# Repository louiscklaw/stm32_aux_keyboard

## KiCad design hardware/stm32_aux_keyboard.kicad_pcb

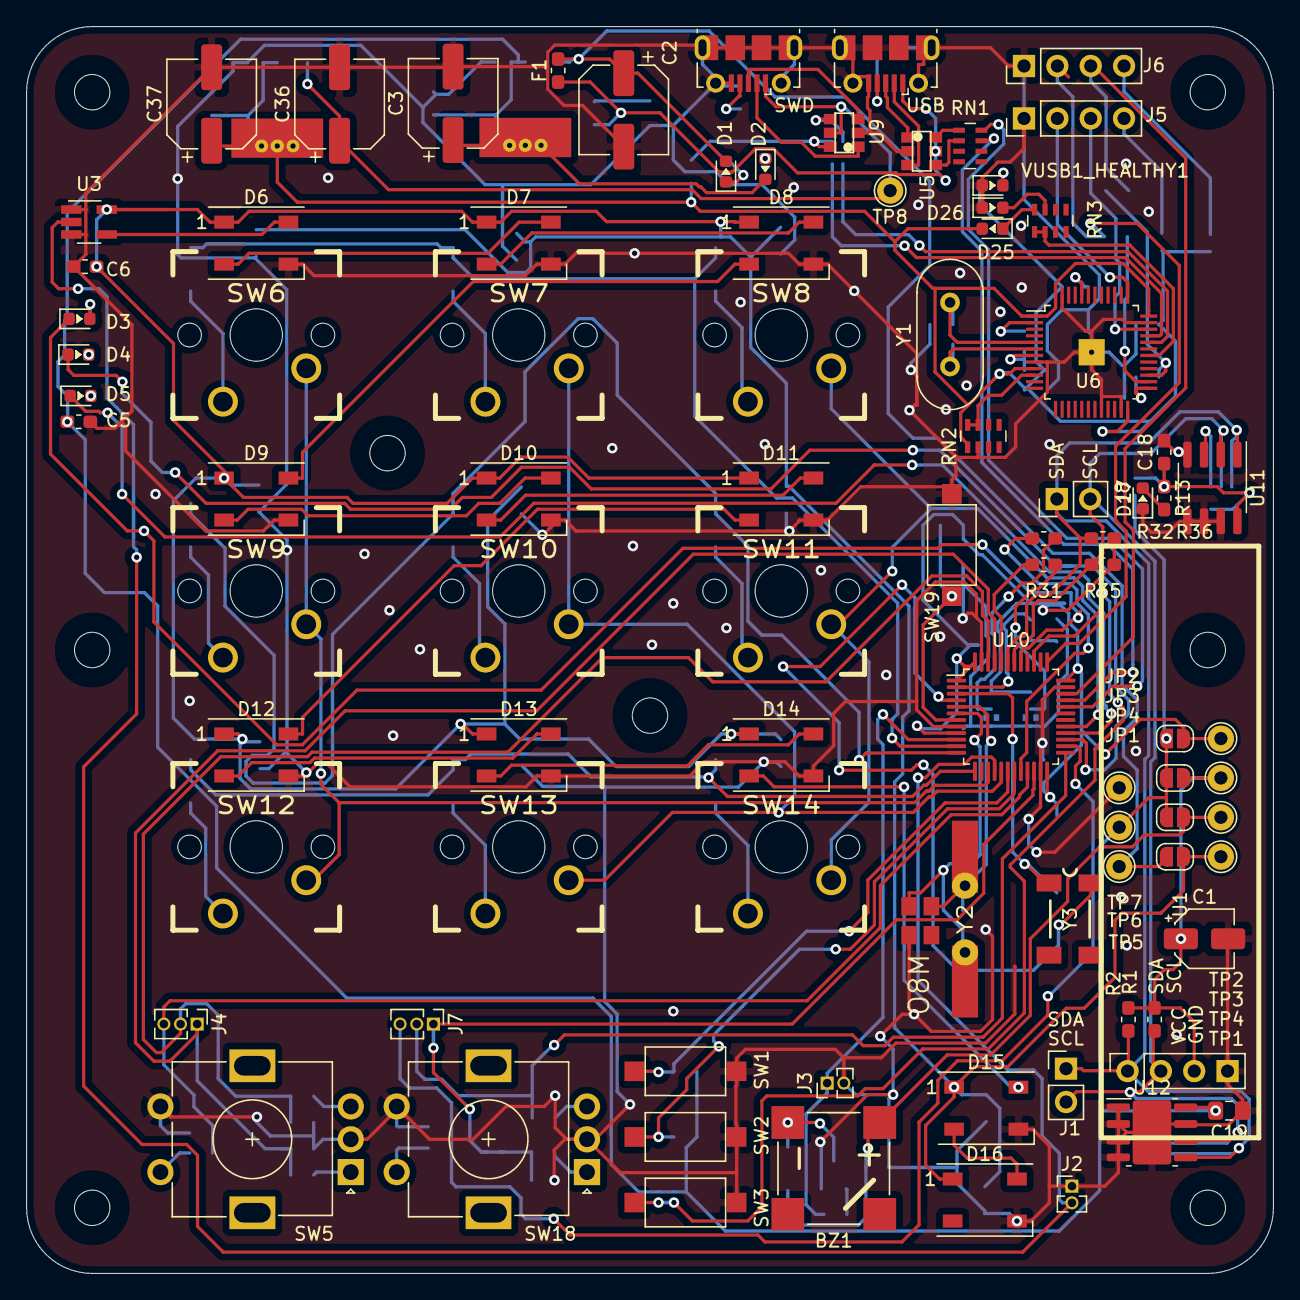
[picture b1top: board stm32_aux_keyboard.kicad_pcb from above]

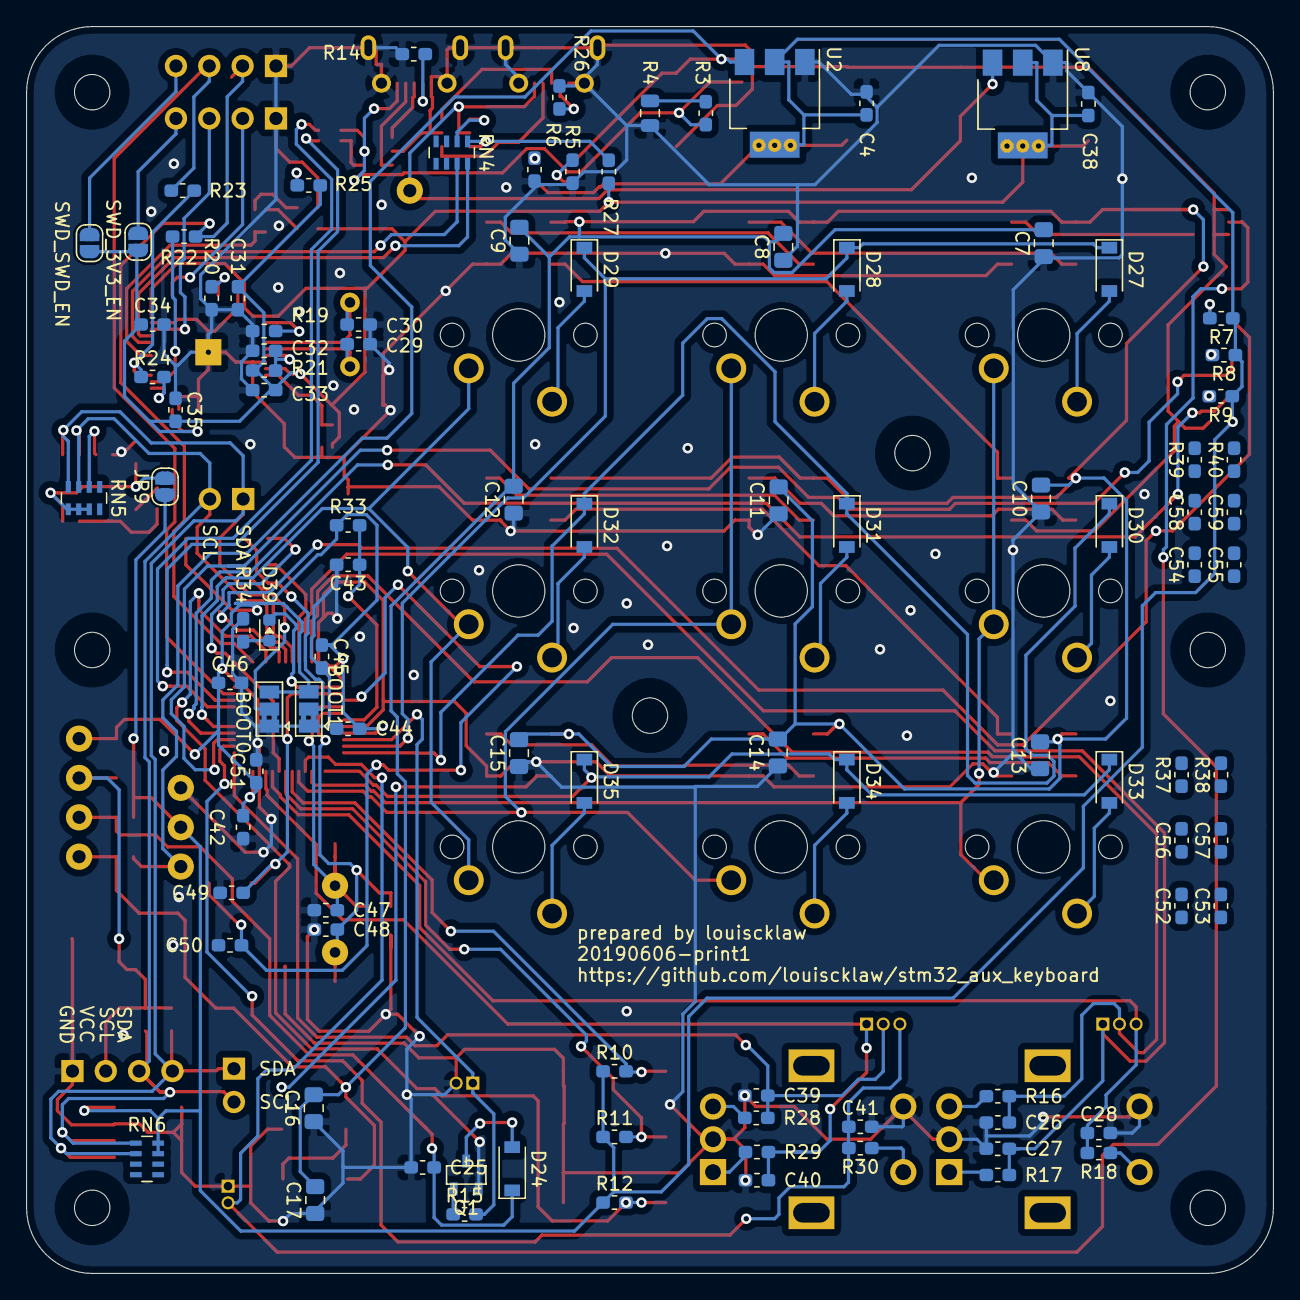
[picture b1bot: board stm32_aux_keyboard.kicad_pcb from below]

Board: 2 copper layers, 95.0 x 95.0 mm, 197 parts (100 on the bottom side), 113 nets.

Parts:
BZ1: BUZZER,MLT-8530; MLT-8530
C1: CP10uf,16V; CP_Elec_4x5.3
C2, C3, C36, C37: CP100uf,16V; CP_Elec_6.3x5.3
C4, C38: C105; C_0603_1608Metric_Pad1.05x0.95mm_HandSolder
C5, C6, C25: C106,0603; C_0603_1608Metric_Pad1.05x0.95mm_HandSolder
C7, C8, C9, C10, C11, C12, C13, C14, C15, C16, C17, C19: C106,0805; C_0805_2012Metric_Pad1.15x1.40mm_HandSolder
C18: C103,0603; C_0603_1608Metric_Pad1.05x0.95mm_HandSolder
C26, C27, C28, C31, C32, C33, C34, C35, C39, C40, C41, C42, C44, C45, C46, C51: C104,0603; C_0603_1608Metric_Pad1.05x0.95mm_HandSolder
C29, C30: C20pf,0603; C_0603_1608Metric_Pad1.05x0.95mm_HandSolder
C43: C105,0603; C_0603_1608Metric_Pad1.05x0.95mm_HandSolder
C47, C48, C49, C50: C20pf; C_0603_1608Metric_Pad1.05x0.95mm_HandSolder
C52, C53, C54, C55, C56, C57, C58, C59: SPARE,0603; C_0603_1608Metric_Pad1.05x0.95mm_HandSolder
D1: LED_GREEN; LED_0603_1608Metric
D2: LED_ORANGE; LED_0603_1608Metric
D3: USR_LED_1; LED_0603_1608Metric
D4: USR_LED_2; LED_0603_1608Metric
D5: USR_LED_3; LED_0603_1608Metric
D6, D7, D8, D9, D10, D11, D12, D13, D14, D15, D16: WS2812B; LED_WS2812B_5050_white
D17, D25: LED_GREEN,0603; LED_0603_1608Metric
D24, D27, D28, D29, D30, D31, D32, D33, D34, D35: D_1N4148_T4; D_SOD-123
D26: LED_RED,0603; LED_0603_1608Metric
D39: PC13; LED_0603_1608Metric
F1: Fuse_Small; R_0603_1608Metric_Pad1.05x0.95mm_HandSolder
H1, H2, H3, H4, H5, H6, H7, H8: MOUNT_M2; MountingHole_2.7mm_M2.5,rpi_like
J1, J8: I2C_HEADER,2.54; I2C_DEBUG,2.54
J2: WS2812_HEADER; PinHeader_1x02_P1.27mm_Vertical
J3: BUZZER_HEADER; PinHeader_1x02_P1.27mm_Vertical
J4, J7: ROT_ENC_HEADER; PinHeader_1x03_P1.27mm_Vertical
J5, J6: SWD_SWD; BLUEPILL_SWD
JP1: WS2812_EN; SolderJumper-2_P1.3mm_Open_RoundedPad1.0x1.5mm
JP2: STM32_EN; SolderJumper-2_P1.3mm_Open_RoundedPad1.0x1.5mm
JP3: OLED_EN; SolderJumper-2_P1.3mm_Open_RoundedPad1.0x1.5mm
JP4: BUZZER_EN; SolderJumper-2_P1.3mm_Open_RoundedPad1.0x1.5mm
JP5: SWD_3V3_EN; SolderJumper-2_P1.3mm_Open_RoundedPad1.0x1.5mm
JP6: SWD_SWD_EN; SolderJumper-2_P1.3mm_Open_RoundedPad1.0x1.5mm
JP7: BOOT0; SolderJumper-3_P1.3mm_Bridged2Bar12_Pad1.0x1.5mm
JP8: BOOT1; SolderJumper-3_P1.3mm_Bridged2Bar12_Pad1.0x1.5mm
JP9: EN; SolderJumper-2_P1.3mm_Open_RoundedPad1.0x1.5mm
Q1: SS9013_J3; 9013,J3,SOT23
R1, R2, R35, R36: R472,0603; R_0603_1608Metric_Pad1.05x0.95mm_HandSolder
R3, R37, R38, R39, R40: R0,0603; R_0603_1608Metric_Pad1.05x0.95mm_HandSolder
R4: VAR_5V6,0805; VAR_0805
R5, R6, R34: R511,0603; R_0603_1608Metric_Pad1.05x0.95mm_HandSolder
R7, R8, R9, R10, R11, R12, R13, R33: R103,0603; R_0603_1608Metric_Pad1.05x0.95mm_HandSolder
R14, R19, R20, R21, R26: R104,0603; R_0603_1608Metric_Pad1.05x0.95mm_HandSolder
R15: R471,0603; R_0603_1608Metric_Pad1.05x0.95mm_HandSolder
R16, R17, R18, R28, R29, R30: R273,0603; R_0603_1608Metric_Pad1.05x0.95mm_HandSolder
R22, R23: R220,0603; R_0603_1608Metric_Pad1.05x0.95mm_HandSolder
R24: R101,0603; R_0603_1608Metric_Pad1.05x0.95mm_HandSolder
R25: R221,0603; R_0603_1608Metric_Pad1.05x0.95mm_HandSolder
R27: R152,0603; R_0603_1608Metric_Pad1.05x0.95mm_HandSolder
R31, R32: R104; R_0603_1608Metric_Pad1.05x0.95mm_HandSolder
RN1: RN_220,0603; R_Array_Concave_4x0603
RN2, RN5, RN6: RN_472,0603; R_Array_Concave_4x0603
RN3, RN4: RN_221,0603; R_Array_Concave_4x0603
SW1: USR_BTN_1; SW_SPST_CK_RS282G05A3
SW2: USR_BTN_2; SW_SPST_CK_RS282G05A3
SW3: USR_BTN_3; SW_SPST_CK_RS282G05A3
SW5: ROT2; RotaryEncoder_Alps_EC11E_Vertical_H20mm
SW6: KEY11; cherry_mx_without_led_100H
SW7: KEY12; cherry_mx_without_led_100H
SW8: KEY13; cherry_mx_without_led_100H
SW9: KEY21; cherry_mx_without_led_100H
SW10: KEY22; cherry_mx_without_led_100H
SW11: KEY23; cherry_mx_without_led_100H
SW12: KEY31; cherry_mx_without_led_100H
SW13: KEY32; cherry_mx_without_led_100H
SW14: KEY33; cherry_mx_without_led_100H
SW18: ROT1; RotaryEncoder_Alps_EC11E_Vertical_H20mm
SW19: SW_RESET,2_leg,SMD; SW_SPST_CK_RS282G05A3
TP1: TP_WS2812; TestPoint_THTPad_D2.0mm_Drill1.0mm
TP2: TP_STM32; TestPoint_THTPad_D2.0mm_Drill1.0mm
TP3: TP_OLED; TestPoint_THTPad_D2.0mm_Drill1.0mm
TP4: TP_BUZZER; TestPoint_THTPad_D2.0mm_Drill1.0mm
TP5: TP_5V; TestPoint_THTPad_D2.0mm_Drill1.0mm
TP6: TP_3V3; TestPoint_THTPad_D2.0mm_Drill1.0mm
TP7: TP_GND; TestPoint_THTPad_D2.0mm_Drill1.0mm
TP8: TP_VUSB1; TestPoint_THTPad_D2.0mm_Drill1.0mm
U1: SSD1306-OLED-I2C; SSD1306_OLED-0.91-128x32_4pin
U2, U8: AMS1117-3.3; AMS1117_SOT-223
U3: 74AHCT1G125; SOT-23-5_HandSoldering
U4: USB; USB_Micro-B_Molex-105017-0001
U5, U9: USBLC6-2SC6_SOT23-6
U6: STM32F103C8T6_rect; STM32F103C8T6
U7: SWD; USB_Micro-B_Molex-105017-0001
U10: STM32F103C8T6; LQFP-48_7x7mm_P0.5mm
U11: LM75; SOP-8_3.76x4.96mm_P1.27mm
U12: 24C02_SOIC8; 24Cxx_SOIC8
VUSB1_HEALTHY1: LED_GREEN,0603; LED_0603_1608Metric
Y1: O_8M; Crystal_HC49-4H_Vertical
Y2: O8M; osc_debug
Y3: O_EPSON_32.768K; MC-306

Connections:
+3V3: C3.1, C4.1, C5.1, C19.2, D2.2, JP2.2, JP3.2, JP4.2, JP9.1, R7.1, R8.1, R9.1, R10.1, R11.1, R12.1, RN6.7, RN6.8, TP6.1, U2.2, U12.8
+5V: C2.1, D1.2, F1.2, JP1.2, TP5.1, U2.3
/24cxx/SCL: J1.SCL, J8.SCL, R1.2, R35.1, RN5.3, RN6.1, U1.SCL, U10.42, U11.2, U12.6
/24cxx/SDA: J1.SDA, J8.SDA, R2.2, R36.1, RN5.4, RN6.2, U1.SDA, U10.43, U11.1, U12.5
/WS2812/WS2812_IN: J2.2, U3.2, U10.16
/keyboard_key/COL1: SW6.2, SW9.2, SW12.2, U10.15
/keyboard_key/COL2: SW7.2, SW10.2, SW13.2, U10.17
/keyboard_key/COL3: SW8.2, SW11.2, SW14.2, U10.29
/keyboard_key/ROW1: D27.1, D28.1, D29.1, U10.11
/keyboard_key/ROW2: D30.1, D31.1, D32.1, U10.12
/keyboard_key/ROW3: D33.1, D34.1, D35.1, U10.13
/rot_enc2/A: C27.1, J4.1, R17.2, U10.45
/rot_enc2/B: C26.1, J4.2, R16.2, U10.46
/rot_enc/A: C40.1, J7.1, R29.2, U10.22
/rot_enc/B: C39.1, J7.2, R28.2, U10.25
/status_display/USR_LED_1: D3.1, U10.41
/status_display/USR_LED_2: D4.1, U10.27
/status_display/USR_LED_3: D5.1, U10.28
/stm32_core/BOOT0: R31.2, U10.44
/stm32_core/BOOT1: R32.1, U10.20
/stm32_core/BUZZER: J3.1, R15.2, U10.10
/stm32_core/OSC32K_N: C50.1, U10.4, Y3.4
/stm32_core/OSC32K_P: C49.1, U10.3, Y3.1
/stm32_core/OSC_N: C48.1, U10.6, Y2.3
/stm32_core/OSC_P: C47.1, U10.5, Y2.1
/stm32_core/PC13: D39.2, U10.2
/stm32_core/RESET: C43.1, R33.2, SW19.2, U10.7
/stm32_core/ROT_ENC_SW1: C28.1, J4.3, R18.2, U10.21
/stm32_core/ROT_ENC_SW2: C41.1, J7.3, R30.2, U10.26
/stm32_core/USB_N: RN1.8, U10.32
/stm32_core/USB_P: RN1.7, U10.33
/stm32_core/USR_BTN1: R10.2, SW1.1, U10.18
/stm32_core/USR_BTN2: R11.2, SW2.1, U10.19
/stm32_core/USR_BTN3: R12.2, SW3.1, U10.39
/stm32_swd/D_SWCLK: J6.2, R22.1, U10.37
/stm32_swd/D_SWDIO: J6.3, R23.1, U10.34
/stm32_swd/LED_STLINK: RN3.1, RN3.2, U6.30
/stm32_swd/SWCLK: J5.2, U6.37
/stm32_swd/SWDIO: J5.3, U6.34
/stm32_swd/T_JTCK: R22.2, U6.26
/stm32_swd/T_JTMS: R23.2, R24.1, U6.27
/stm32_swd/USB_N: RN4.7, U6.32
/stm32_swd/USB_P: RN4.8, U6.33
GND: C1.2, C2.2, C3.2, C4.2, C5.2, C6.1, C7.1, C8.1, C9.1, C10.1, C11.1, C12.1, C13.1, C14.1, C15.1, C16.1, C17.1, C18.2, C19.1, C25.2, C26.2, C27.2, C28.2, C29.1, C30.1, C31.2, C32.2, C33.1, C34.2, C35.1, C36.2, C37.2, C38.2, C39.2, C40.2, C41.2, C42.2, C43.2, C44.2, C45.2, C46.2, C47.2, C48.2, C49.2, C50.2, C51.2, D6.3, D7.3, D8.3, D9.3, D10.3, D11.3, D12.3, D13.3, D14.3, D15.3, D16.3, D17.1, D26.1, J2.1, J3.2, J5.1, J6.1, JP7.1, JP8.1, Q1.2, R4.2, R5.2, R6.2, R14.2, R19.1, R20.1, R26.2, R34.2, RN2.2, SW1.2, SW2.2, SW3.2, SW5.C, SW5.E, SW18.C, SW18.E, SW19.1, TP7.1, U1.GND, U2.1, U3.1, U3.3, U4.5, U4.6, U4.7, U4.8, U4.9, U5.2, U6.8, U6.20, U6.23, U6.35, U6.47, U7.5, U7.6, U7.7, U7.8, U7.9, U8.1, U9.2, U10.8, U10.23, U10.35, U10.47, U11.4, U11.5, U11.6, U11.7, U12.1, U12.2, U12.3, U12.4, U12.7, VUSB1_HEALTHY1.1, Y2.2
unnamed: BZ1.N, D24.2, Q1.3
unnamed: C18.1, JP9.2, R13.1, RN5.5, RN5.6, RN5.7, U11.8
unnamed: C29.2, U6.6, Y1.1
unnamed: C30.2, U6.5, Y1.2
unnamed: C32.1, R21.2, U6.7
unnamed: D1.1, R5.1
unnamed: D2.1, R6.1
unnamed: D3.2, R7.2
unnamed: D4.2, R8.2
unnamed: D5.2, R9.2
unnamed: D6.2, D7.4
unnamed: D6.4, U3.4
unnamed: D7.2, D8.4
unnamed: D8.2, D9.4
unnamed: D10.2, D11.4
unnamed: D9.2, D10.4
unnamed: D11.2, D12.4
unnamed: D12.2, D13.4
unnamed: D13.2, D14.4
unnamed: D14.2, D15.4
unnamed: D15.2, D16.4
unnamed: D17.2, R13.2
unnamed: D25.1, RN3.8
unnamed: D26.2, RN3.7
unnamed: D27.2, SW6.1
unnamed: D28.2, SW7.1
unnamed: D29.2, SW8.1
unnamed: D30.2, SW9.1
unnamed: D31.2, SW10.1
unnamed: D32.2, SW11.1
unnamed: D33.2, SW12.1
unnamed: D34.2, SW13.1
unnamed: D35.2, SW14.1
unnamed: D39.1, R34.1
unnamed: J5.4, JP5.2
unnamed: J6.4, JP6.2
unnamed: RN5.2, U11.3
unnamed: JP7.2, R31.1
unnamed: JP8.2, R32.2
unnamed: Q1.1, R15.1
unnamed: R3.2, R4.1
unnamed: R14.1, U4.4
unnamed: R16.1, SW5.B
unnamed: R17.1, SW5.A
unnamed: R18.1, SW5.D
unnamed: R19.2, U6.2
unnamed: R20.2, U6.44
unnamed: R24.2, U6.25
unnamed: R25.1, VUSB1_HEALTHY1.2
unnamed: R26.1, U7.4
unnamed: R27.2, RN4.1, U9.6
unnamed: R28.1, SW18.B
unnamed: R29.1, SW18.A
unnamed: R30.1, SW18.D
unnamed: RN1.1, U5.6
unnamed: RN1.2, U5.4
unnamed: RN2.7, RN2.8, U6.10
unnamed: RN4.2, U9.4
unnamed: U4.2, U5.3
unnamed: U4.3, U5.1
unnamed: U7.2, U9.1
unnamed: U7.3, U9.3
VCC: C6.2, C7.2, C8.2, C9.2, C10.2, C11.2, C12.2, C13.2, C14.2, C15.2, C16.2, C17.2, D6.1, D7.1, D8.1, D9.1, D10.1, D11.1, D12.1, D13.1, D14.1, D15.1, D16.1, JP1.1, TP1.1, U3.5
Vbuzzer: BZ1.P, C25.1, D24.1, JP4.1, TP4.1
Voled: C1.1, JP3.1, R1.1, R2.1, TP3.1, U1.VCC
Vstm32: C42.1, C44.1, C45.1, C46.1, C51.1, JP2.1, JP7.3, JP8.3, R33.1, R35.2, R36.2, TP2.1, U10.1, U10.9, U10.24, U10.36, U10.48
Vstm32_stlink: C31.1, C33.2, C34.1, C35.2, C37.1, C38.1, D25.2, JP5.1, JP6.1, R21.1, R25.2, R27.1, RN2.1, U6.1, U6.9, U6.24, U6.36, U6.48, U8.2
Vusb: F1.1, R3.1, U4.1, U5.5
Vusb_1: C36.1, TP8.1, U7.1, U8.3, U9.5

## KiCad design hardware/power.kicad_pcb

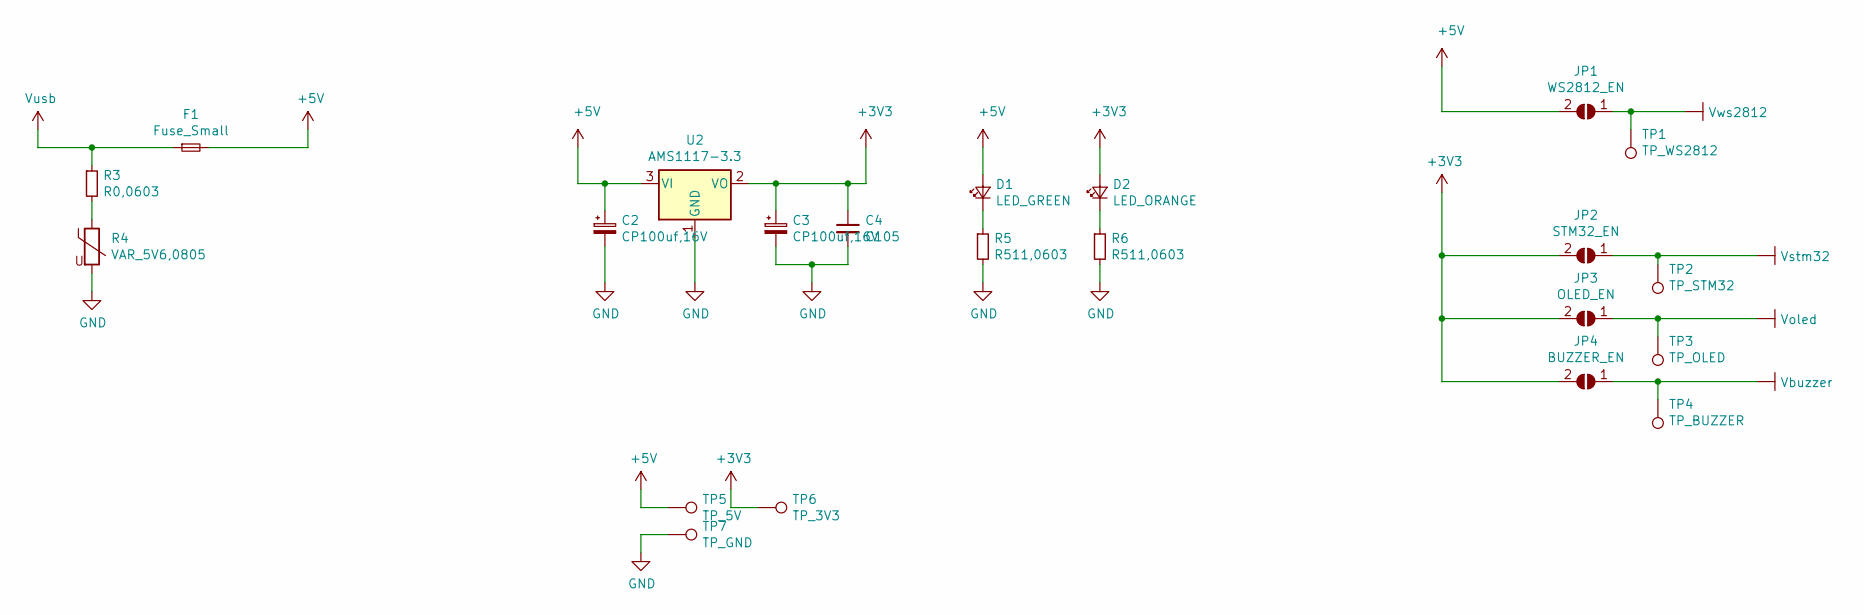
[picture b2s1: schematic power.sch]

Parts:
C2, C3: CP100uf,16V; CP_Elec_6.3x5.3
C4: C105; C_0603_1608Metric_Pad1.05x0.95mm_HandSolder
D1: LED_GREEN; LED_0805_2012Metric_Pad1.15x1.40mm_HandSolder
D2: LED_ORANGE; LED_0805_2012Metric_Pad1.15x1.40mm_HandSolder
F1: Fuse_Small; R_0603_1608Metric_Pad1.05x0.95mm_HandSolder
JP1: WS2812_EN; SolderJumper-2_P1.3mm_Open_RoundedPad1.0x1.5mm
JP2: STM32_EN; SolderJumper-2_P1.3mm_Open_RoundedPad1.0x1.5mm
JP3: OLED_EN; SolderJumper-2_P1.3mm_Open_RoundedPad1.0x1.5mm
JP4: BUZZER_EN; SolderJumper-2_P1.3mm_Open_RoundedPad1.0x1.5mm
R3: R0,0603; R_0603_1608Metric_Pad1.05x0.95mm_HandSolder
R4: VAR_5V6,0805; VAR_0805
R5, R6: R511,0603; R_0603_1608Metric_Pad1.05x0.95mm_HandSolder
TP1: TP_WS2812; TestPoint_THTPad_D2.0mm_Drill1.0mm
TP2: TP_STM32; TestPoint_THTPad_D2.0mm_Drill1.0mm
TP3: TP_OLED; TestPoint_THTPad_D2.0mm_Drill1.0mm
TP4: TP_BUZZER; TestPoint_THTPad_D2.0mm_Drill1.0mm
TP5: TP_5V; TestPoint_THTPad_D2.0mm_Drill1.0mm
TP6: TP_3V3; TestPoint_THTPad_D2.0mm_Drill1.0mm
TP7: TP_GND; TestPoint_THTPad_D2.0mm_Drill1.0mm
U2: AMS1117-3.3; SOT-223-3_TabPin2

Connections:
+3V3: C3.1, C4.1, D2.2 (A), JP2.2 (B), JP3.2 (B), JP4.2 (B), TP6.1, U2.2 (VO)
+5V: C2.1, D1.2 (A), F1.2, JP1.2 (B), TP5.1, U2.3 (VI)
GND: C2.2, C3.2, C4.2, R4.2, R5.2, R6.2, TP7.1, U2.1 (GND)
unnamed: D1.1 (K), R5.1
unnamed: D2.1 (K), R6.1
unnamed: R3.2, R4.1
Vbuzzer: JP4.1 (A), TP4.1
Voled: JP3.1 (A), TP3.1
Vstm32: JP2.1 (A), TP2.1
Vusb: F1.1, R3.1
Vws2812: JP1.1 (A), TP1.1

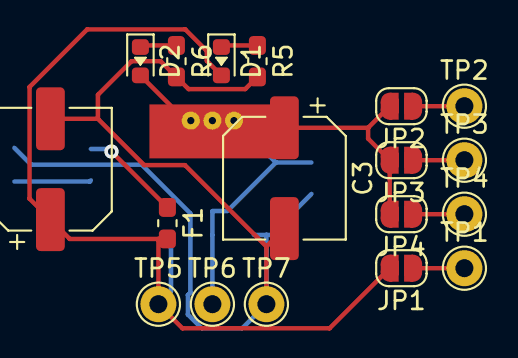
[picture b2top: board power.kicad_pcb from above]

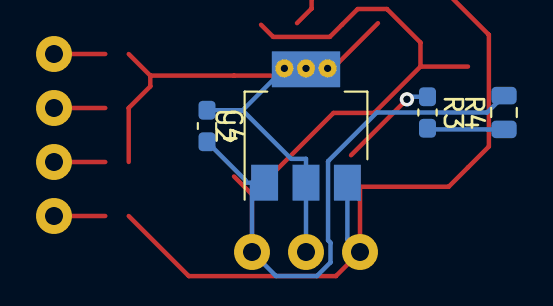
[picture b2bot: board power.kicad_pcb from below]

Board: 2 copper layers, 22 parts (4 on the bottom side), 11 nets.

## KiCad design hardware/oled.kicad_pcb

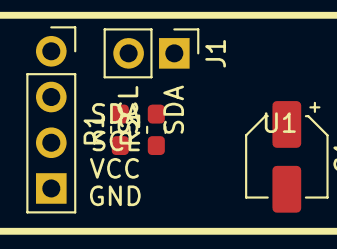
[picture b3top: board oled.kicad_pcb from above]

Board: 2 copper layers, 5 parts (0 on the bottom side), 4 nets, no tracks yet.

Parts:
C1: CP10uf,16V; CP_Elec_4x5.3
J1: I2C_HEADER,2.54; I2C_DEBUG,2.54
R1, R2: R472,0603; R_0603_1608Metric_Pad1.05x0.95mm_HandSolder
U1: SSD1306-OLED-I2C; SSD1306_OLED-0.91-128x32_4pin

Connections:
/SCL: J1.SCL, R1.2, U1.SCL
/SDA: J1.SDA, R2.2, U1.SDA
GND: C1.2, U1.GND
Voled: C1.1, R1.1, R2.1, U1.VCC

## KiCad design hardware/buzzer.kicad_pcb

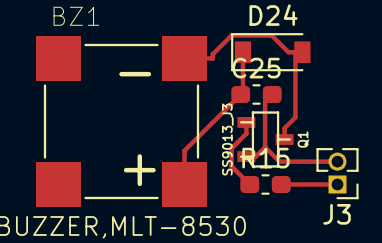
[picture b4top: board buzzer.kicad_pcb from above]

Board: 2 copper layers, 6 parts (0 on the bottom side), 5 nets.

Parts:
BZ1: BUZZER,MLT-8530; MLT-8530
C25: C106,0603; C_0603_1608Metric_Pad1.05x0.95mm_HandSolder
D24: D_1N4148_T4; D_SOD-123
J3: BUZZER_HEADER; PinHeader_1x02_P1.27mm_Vertical
Q1: SS9013_J3; 9013,J3,SOT23
R15: R471,0603; R_0603_1608Metric_Pad1.05x0.95mm_HandSolder

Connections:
/BUZZER_IN: J3.1, R15.2
GND: C25.2, J3.2, Q1.2
unnamed: BZ1.N, D24.2, Q1.3
unnamed: Q1.1, R15.1
Vbuzzer: BZ1.P, C25.1, D24.1

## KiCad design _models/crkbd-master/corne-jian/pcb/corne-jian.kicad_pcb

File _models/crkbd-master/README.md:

# crkbd x jian

This is a fork of the corne-chocolate PCB, with some small tweaks to its physical layout, as well as a custom-designed case and keycaps. All files can be found under the corne-jian/ subdirectory.

The PCB was edited in KiCAD 5. Following changes were made:
- change PCB edge shapes
- change choc switch footprints from hot-swap to PCB-mount
- change mounting holes locations & dimensions
- add 3D models for some components

The case and keycaps were designed in FreeCAD 0.17. The case has some holes for M2 inserts to be added, into which the PCB should then be screwed. The holes turned out to be slightly too large for my inserts, so I had to add some super glue. The keycaps work reasonably well given that they are FDM printed with PETG filament, but they wobble a bit in the switches and should probably be re-printed using resin in an SLA printer.

## Original variants

These are unchanged from foostan's original repo:
- corne-classic
- corne-cherry: Hotswappable corne for CherryMX switches by kailh PCB sockets.
- corne-chocolate: Hotswappable corne for Chocolate switches by kailh PCB sockets.
- corne-light: Lightweight corne(Easily build and Simply PCB).

## Photos

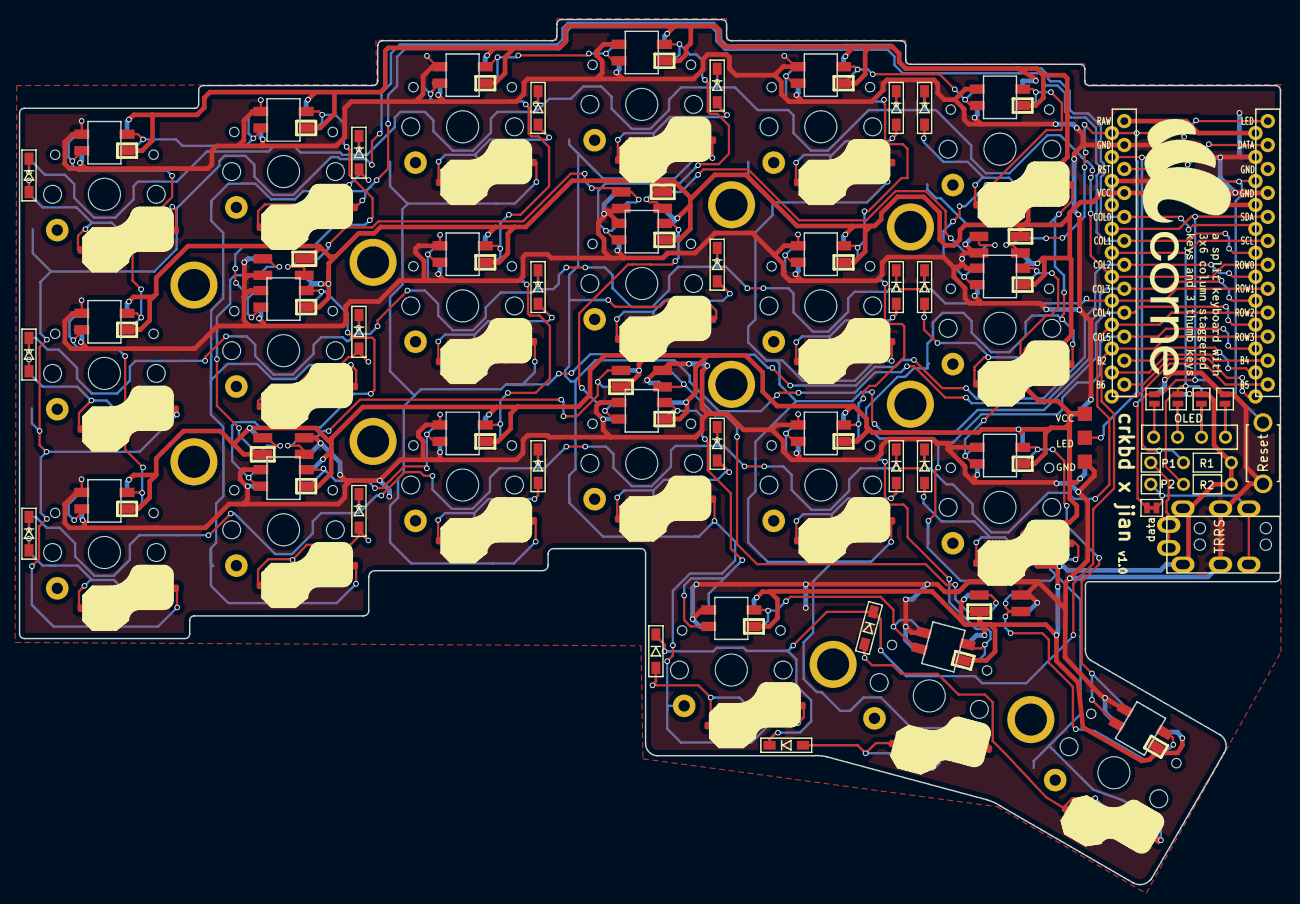
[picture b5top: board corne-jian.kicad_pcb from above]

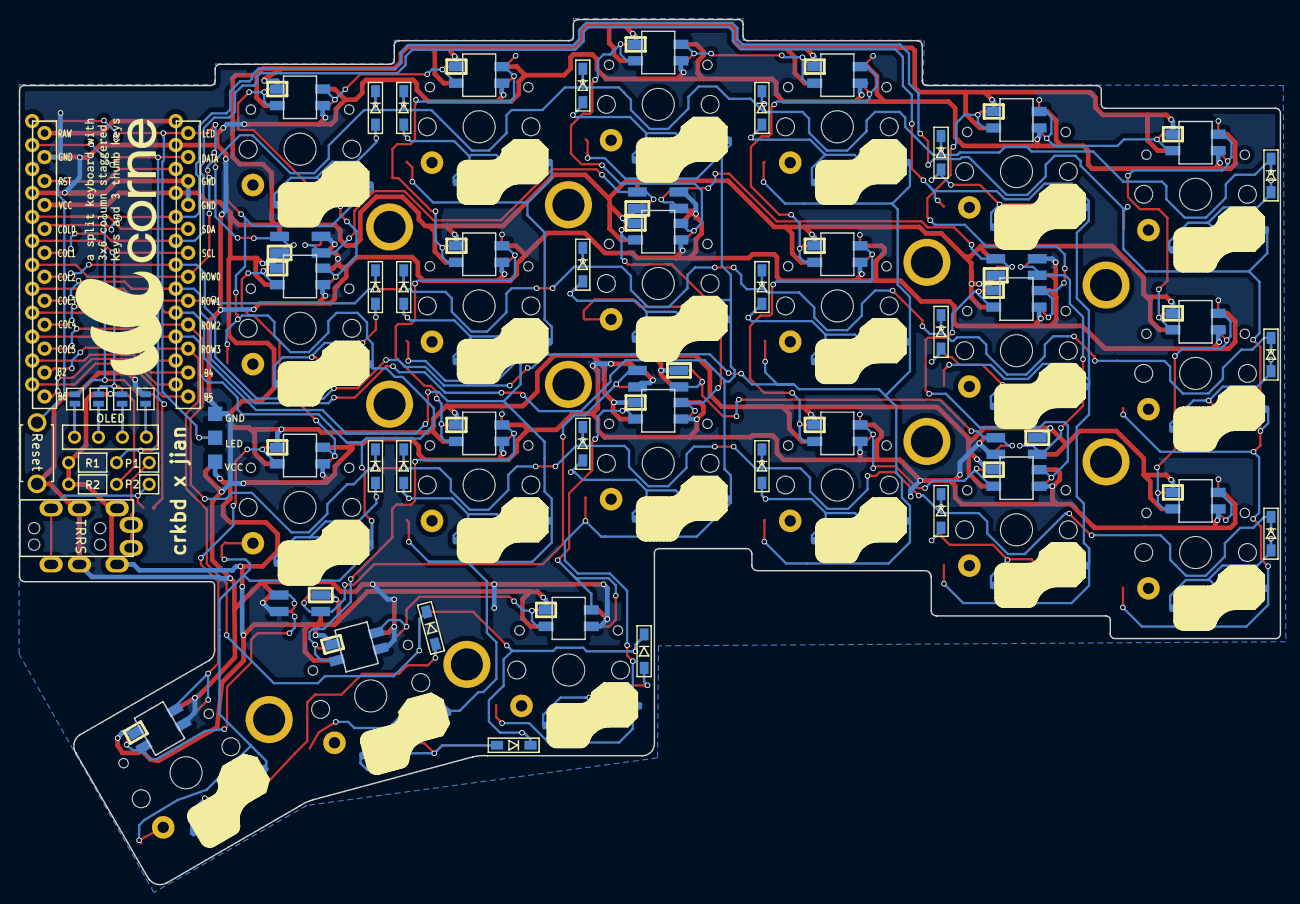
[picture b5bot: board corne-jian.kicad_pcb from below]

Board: 2 copper layers, 133.8 x 91.8 mm, 87 parts (4 on the bottom side), 70 nets.

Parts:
D1, D2, D3, D4, D5, D6, D7, D8, D9, D10, D11, D12, D13, D14, D15, D16, D17, D18, D19, D20, D21: D; D3_SMD
J3: LED; StripLED_rev
JP2, JP3, JP4, JP5, JP6, JP7, JP8, JP9: Jumper
L1, L2, L3, L4, L5, L6, L7, L8, L9, L10, L11, L12, L13, L14, L15, L16, L17, L18, L19, L20, L21: SK6812MINI; SK6812MINI_rev
L22, L23, L24, L25, L26, L27: SK6812MINI; SK6812MINI_underglow_rev
OLED: OLED
P1, P2: i2c-pin; 1pin_conn
R1, R2: R
RSW1: Reset; ResetSW
SW1, SW2, SW3, SW4, SW5, SW6, SW7, SW8, SW9, SW10, SW11, SW12, SW13, SW14, SW15, SW16, SW17, SW18, SW19, SW21: SW_PUSH; Choc_Switch
SW20: SW_PUSH; Choc_Switch_SpecialCap
TRRS: TRRS
U1: ProMicro; ProMicro_v2
data: JPC2

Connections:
GND: J3.1, JP2.1, JP9.1, L1.2, L2.2, L3.2, L4.2, L5.2, L6.2, L7.2, L8.2, L9.2, L10.2, L11.2, L12.2, L13.2, L14.2, L15.2, L16.2, L17.2, L18.2, L19.2, L20.2, L21.2, L22.2, L23.2, L24.2, L25.2, L26.2, L27.2, RSW1.2, TRRS.C, U1.3, U1.4, U1.23
LED: J3.2, L24.3, U1.1
unnamed: D1.2, SW1.2
unnamed: D2.2, SW2.2
unnamed: D3.2, SW3.2
unnamed: D4.2, SW4.2
unnamed: D5.2, SW5.2
unnamed: D6.2, SW6.2
unnamed: D7.2, SW7.2
unnamed: D8.2, SW8.2
unnamed: D9.2, SW9.2
unnamed: D10.2, SW10.2
unnamed: D11.2, SW11.2
unnamed: D12.2, SW12.2
unnamed: D13.2, SW13.2
unnamed: D14.2, SW14.2
unnamed: D15.2, SW15.2
unnamed: D16.2, SW16.2
unnamed: D17.2, SW17.2
unnamed: D18.2, SW18.2
unnamed: D19.2, SW19.2
unnamed: D20.2, SW20.2
unnamed: D21.2, SW21.2
unnamed: P1.1, TRRS.A
unnamed: P2.1, TRRS.B, data.2
unnamed: JP5.2, JP9.2, OLED.1
unnamed: JP4.2, JP8.2, OLED.2
unnamed: JP3.2, JP7.2, OLED.3
unnamed: JP2.2, JP6.2, OLED.4
unnamed: L1.1, L7.3
unnamed: L1.3, L2.1
unnamed: L2.3, L8.1
unnamed: L3.1, L9.3
unnamed: L3.3, L4.1
unnamed: L5.3, L6.1
unnamed: L4.3, L10.1
unnamed: L10.3, L16.1
unnamed: L11.1, L17.3
unnamed: L5.1, L11.3
unnamed: L6.3, L12.1
unnamed: L12.3, L18.1
unnamed: L7.1, L13.3
unnamed: L8.3, L14.1
unnamed: L14.3, L15.1
unnamed: L9.1, L15.3
unnamed: L16.3, L19.1
unnamed: L17.1, L20.3
unnamed: L18.3, L21.1
unnamed: L19.3, L20.1
unnamed: L21.3, L27.1
unnamed: L22.1, L25.3
unnamed: L22.3, L23.1
unnamed: L23.3, L24.1
unnamed: L25.1, L26.3
unnamed: L26.1, L27.3
SCL: JP4.1, JP7.1, R2.2, U1.6
SDA: JP5.1, JP6.1, R1.2, U1.5
VCC: J3.3, JP3.1, JP8.1, L1.4, L2.4, L3.4, L4.4, L5.4, L6.4, L7.4, L8.4, L9.4, L10.4, L11.4, L12.4, L13.4, L14.4, L15.4, L16.4, L17.4, L18.4, L19.4, L20.4, L21.4, L22.4, L23.4, L24.4, L25.4, L26.4, L27.4, R1.1, R2.1, TRRS.D, U1.21
col0: SW1.1, SW7.1, SW13.1, U1.20
col1: SW2.1, SW8.1, SW14.1, U1.19
col2: SW3.1, SW9.1, SW15.1, U1.18
col3: SW4.1, SW10.1, SW16.1, SW19.1, U1.17
col4: SW5.1, SW11.1, SW17.1, SW20.1, U1.16
col5: SW6.1, SW12.1, SW18.1, SW21.1, U1.15
data: U1.2, data.1
reset: RSW1.1, U1.22
row0: D1.1, D2.1, D3.1, D4.1, D5.1, D6.1, U1.7
row1: D7.1, D8.1, D9.1, D10.1, D11.1, D12.1, U1.8
row2: D13.1, D14.1, D15.1, D16.1, D17.1, D18.1, U1.9
row3: D19.1, D20.1, D21.1, U1.10

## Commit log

2019-06-02 update,
2019-06-02 update for cherry key,
2019-06-02 update for cherry key,wd
2019-06-02 update for power symbol,
2019-06-02 update DRC ok,
2019-06-02 update gitignore,
2019-06-02 remote temp file,
2019-06-02 update point schedule,
2019-06-02 update footprint,
2019-06-02 update pre-route,
2019-06-02 update route,
2019-06-02 update rout,
2019-06-02 update for routing,
2019-06-03 update ws2812,
2019-06-03 update remote btn4 and all capacitor in place,
2019-06-03 update for place complete,
2019-06-03 update for add supporting hold,
2019-06-03 update labelling,
2019-06-03 update model,
2019-06-03 update DRC ok, no routing,
2019-06-04 update to ignore bak file,
2019-06-04 updaste,
2019-06-06 update for autoroute complete,
2019-06-06 update for tidy tracks,
2019-06-06 check footprint,
2019-06-06 send to fab,
2019-06-06 prepare to fab,
2020-05-07 ci: init travis build config,
2020-05-07 ci: init travis token,
